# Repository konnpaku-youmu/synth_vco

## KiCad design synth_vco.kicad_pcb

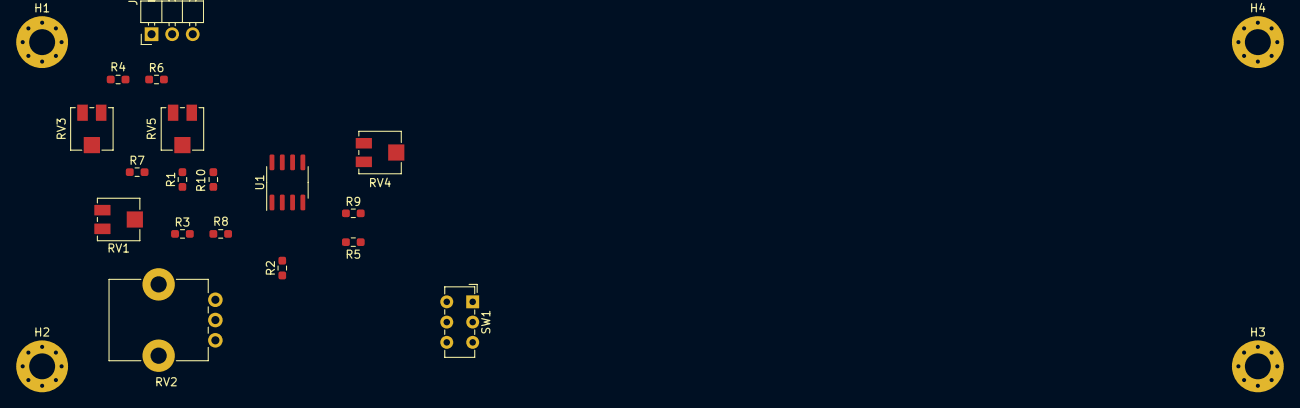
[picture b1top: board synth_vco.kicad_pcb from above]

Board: 2 copper layers, 22 parts (0 on the bottom side), 13 nets, no tracks yet.

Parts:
H1, H2, H3, H4: MountingHole; MountingHole_3.2mm_M3_Pad_Via
J1: PWR; PinHeader_1x03_P2.54mm_Horizontal
R1, R2, R3, R7: 100k; R_0603_1608Metric_Pad0.98x0.95mm_HandSolder
R4: 100; R_0603_1608Metric_Pad0.98x0.95mm_HandSolder
R5: 1k5; R_0603_1608Metric_Pad0.98x0.95mm_HandSolder
R6: 10k; R_0603_1608Metric_Pad0.98x0.95mm_HandSolder
R8: 2k37; R_0603_1608Metric_Pad0.98x0.95mm_HandSolder
R9: 750; R_0603_1608Metric_Pad0.98x0.95mm_HandSolder
R10: 150k; R_0603_1608Metric_Pad0.98x0.95mm_HandSolder
RV1, RV3, RV5: 100k; Potentiometer_Vishay_TS53YJ_Vertical
RV2: 100k; Potentiometer_Alps_RK09K_Single_Vertical
RV4: 200; Potentiometer_Vishay_TS53YJ_Vertical
SW1: SW_SPDT; SW_E-Switch_EG1271_DPDT
U1: TL081; SOIC-8_3.9x4.9mm_P1.27mm

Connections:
+15V: J1.1, R6.2, RV5.3, U1.7
-15V: J1.3, RV1.1, U1.4
/DC_OFFSET: R1.2, R2.2, R3.2, R7.2, R8.2, R10.1, U1.2
GND: J1.2, R4.1, R5.2, R9.1, RV1.3, RV2.3, RV3.3, RV5.1
unnamed: R1.1, RV1.2
unnamed: R2.1, SW1.2
unnamed: R3.1, RV2.2
unnamed: R4.2, R6.1, RV3.1
unnamed: R5.1, U1.3
unnamed: R7.1, RV3.2
unnamed: R8.1, RV4.1, U1.6
unnamed: R9.2, RV4.3
unnamed: R10.2, RV5.2

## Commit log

2021-04-14 message
